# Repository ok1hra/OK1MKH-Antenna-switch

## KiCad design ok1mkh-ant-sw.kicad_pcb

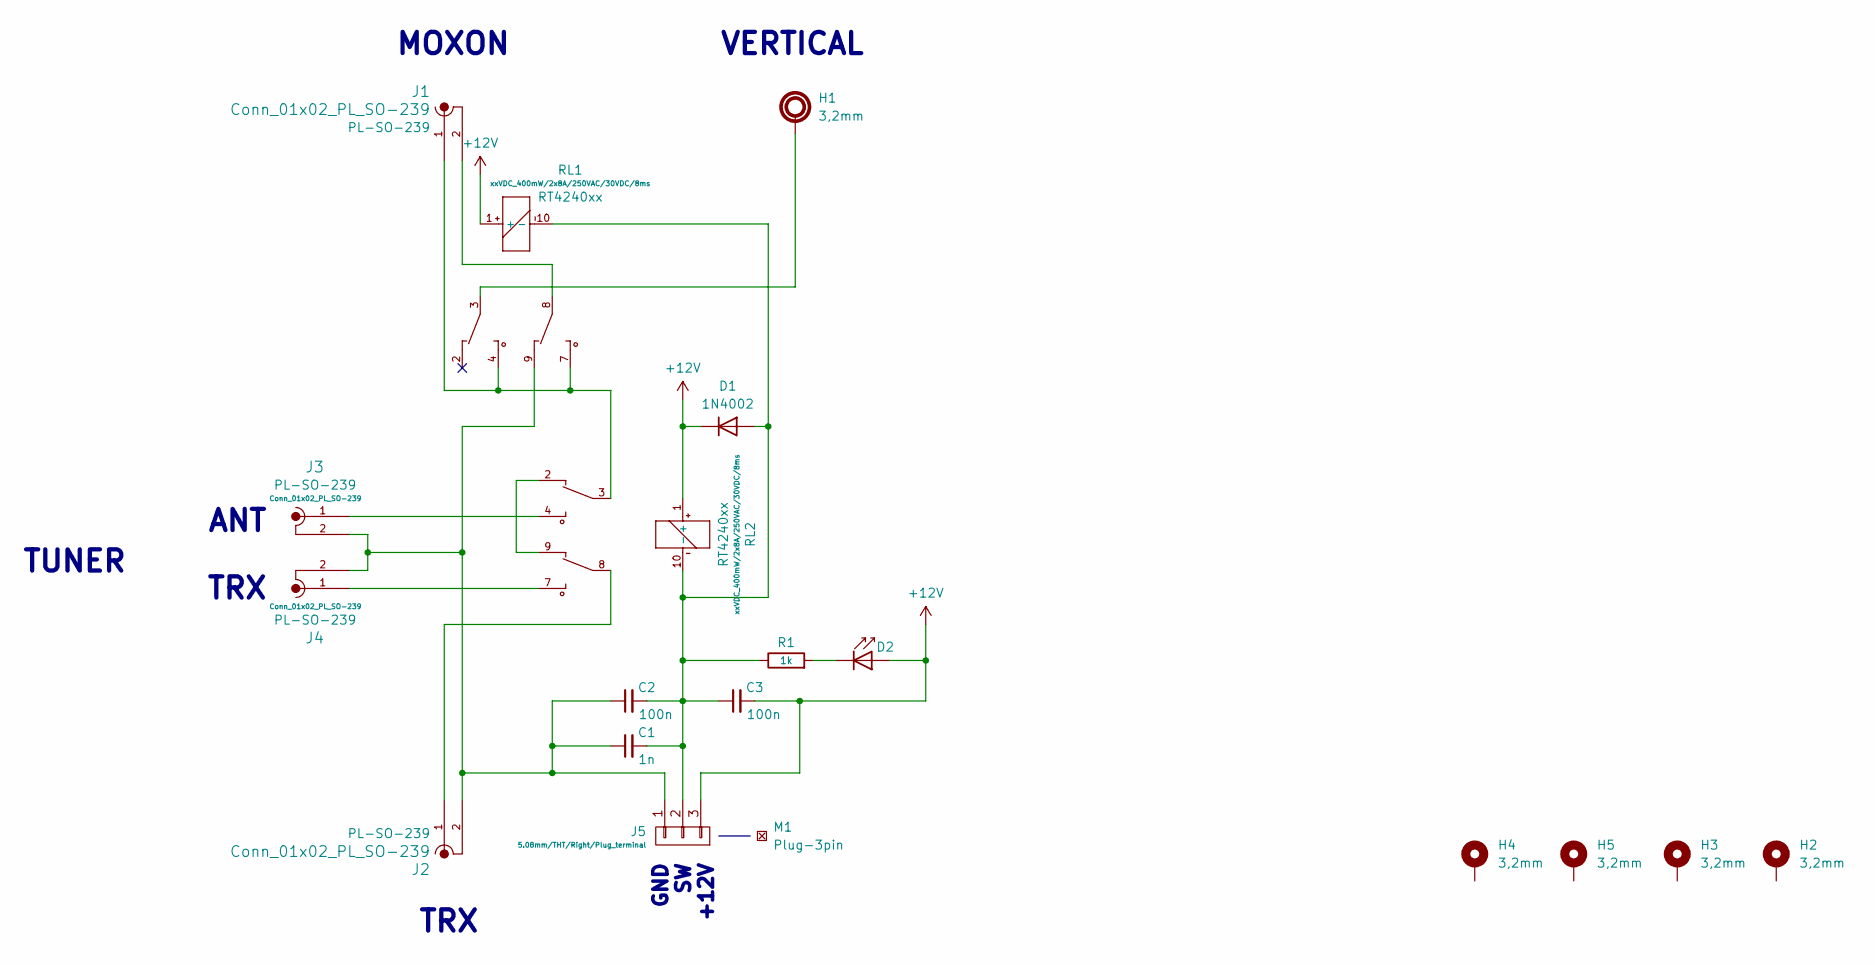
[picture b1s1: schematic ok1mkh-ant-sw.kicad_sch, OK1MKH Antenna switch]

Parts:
C1: C_1n_2kV_1206; C_Disc_D8.0mm_W2.5mm_P5.00mm; part_value 1n
C2, C3: C_1n_2kV_1206; C_Disc_D8.0mm_W2.5mm_P5.00mm; part_value 100n
D1: 1N4002; D_A-405_P10.16mm_Horizontal
D2: LED; LED_D5.0mm
H1: MEC_MountingHole_3.2mm_M3_Pad_Via; MountingHole_3.2mm_M3_Pad_Via; part_value 3,2mm
H2, H3, H4, H5: MEC_MountingHole_3.2mm_M3_ISO7380_Pad; MountingHole_3.2mm_M3_ISO7380_Pad; part_value 3,2mm
J1, J2, J3, J4: Conn_01x02_PL_SO-239; PL-SO-239; part_value PL-SO-239
J5: Conn_01x03_5.08mm_Right_terminal_796638-3; 796638-3; part_value 796638-3
M1: Plug-3pin; MEC
R1: 1k; R_Axial_DIN0204_L3.6mm_D1.6mm_P7.62mm_Horizontal
RL1, RL2: REL_DPDT_2x8A_RT4240xx; REL_RT4240xx; part_value RT4240xx

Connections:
+12V: C3.2, D1.1 (K), D2.2 (A), J5.3, RL1.1 (+), RL2.1 (+)
unnamed: C1.1, C2.1, J2.2, J3.2, J4.2, J5.1, RL1.9
unnamed: C1.2, C2.2, C3.1, D1.2 (A), J5.2, R1.1, RL1.10 (-), RL2.10 (-)
unnamed: D2.1 (K), R1.2
unnamed: H1.1, RL1.3
unnamed: J1.1, RL1.4, RL1.7, RL2.3
unnamed: J1.2, RL1.8
unnamed: J2.1, RL2.8
unnamed: J3.1, RL2.4
unnamed: J4.1, RL2.7
unnamed: RL2.2, RL2.9

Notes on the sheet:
GND SW +12V
VERTICAL
TRX
ANT
MOXON
TUNER

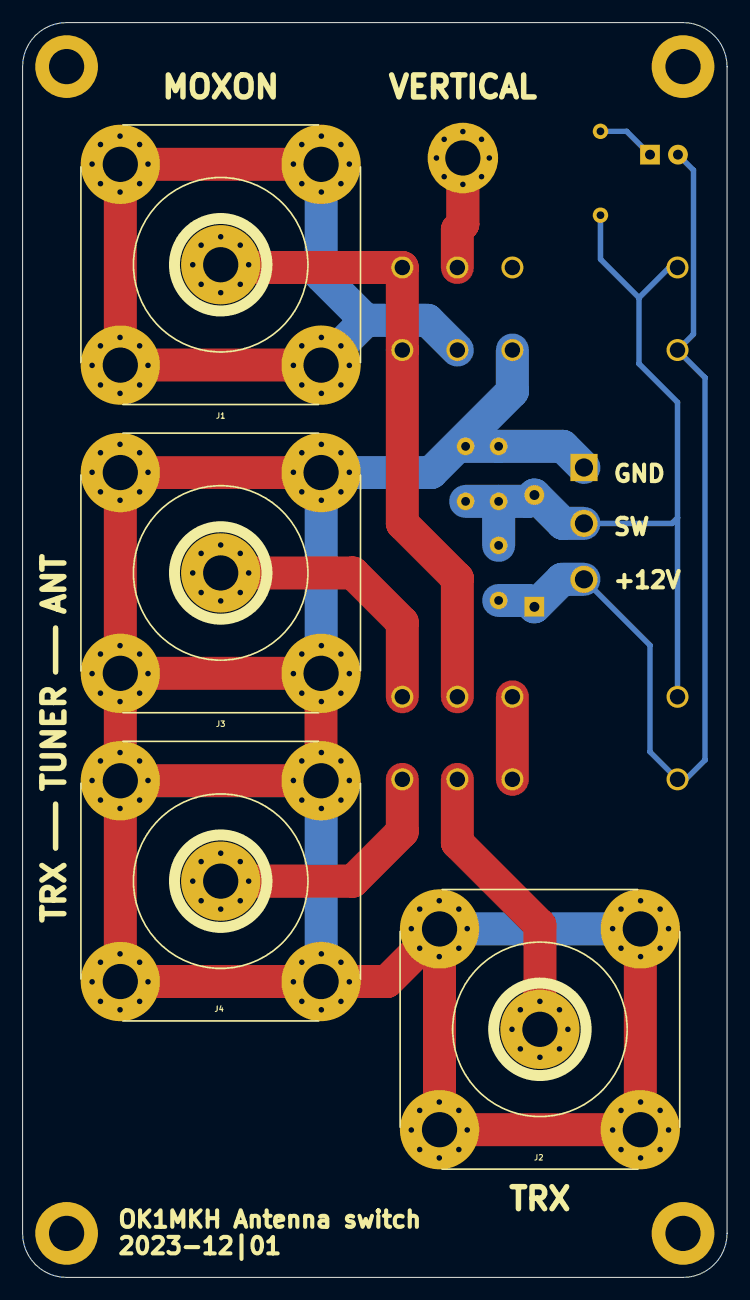
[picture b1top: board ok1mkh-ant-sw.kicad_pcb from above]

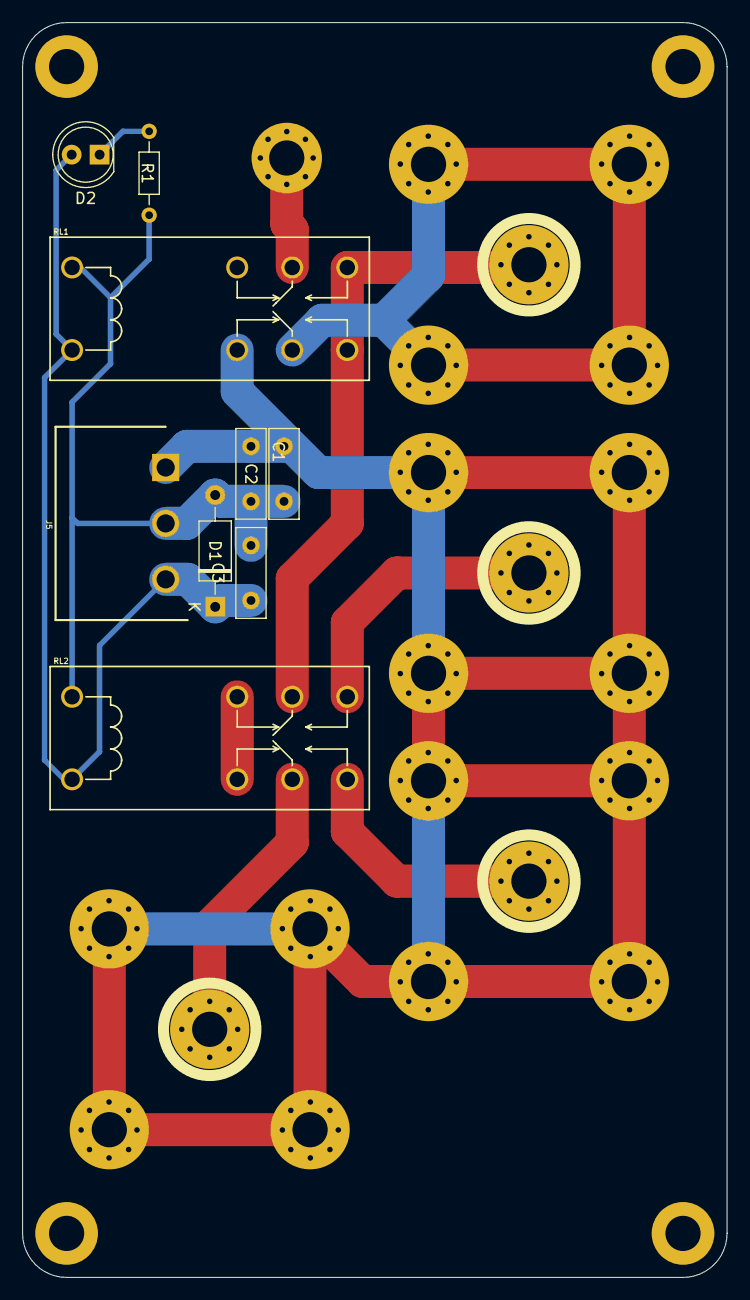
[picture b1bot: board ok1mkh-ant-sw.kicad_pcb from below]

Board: 2 copper layers, 64.0 x 114.0 mm, 18 parts (9 on the bottom side), 11 nets.

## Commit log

2023-12-11 add pic
2023-12-11 readme
